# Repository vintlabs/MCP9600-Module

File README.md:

# MCP9600-Module
MCP9600 I²C Thermocouple to Digital Module (Hardware)

Simple module to detect temperature from a thermocouple on a Raspberry Pi (plugs in directly to the header on a Pi) or Arduino etc.
Supports thermocouple types K, J, T, N, S, E, B and R, and uses simple I²C interface. Can be run on 2.7v to 5.5v.
Board dimensions: 15x28mm (headers protrude beyond that)

There are headers on both sides of the board so that multiple boards can be connected together (being sure to use a different I2C address for each!), and there are footprints to add pullup resistors if they are required. 

Additionally, alerts can be programmed, and when plugged directly into a Raspberry Pi GPIO4 will be ALERT1, ALERT2-4 are accessible using optional header J3.

Note that as of this date, the gerbers are the Rev A prototype and the design is a bit ahead of that. (only minor edits - the Rev A board works fine)

Designed using KiCAD 5.0.0

See pdf/ directory for images and PDF of schematic.

See https://github.com/pvint/MCP9600_Pi for C code (tested on a Raspberry Pi Zero W using a type K thermocouple)

### Here are three boards in action. You can chain up to 8 boards on a single I²C bus.

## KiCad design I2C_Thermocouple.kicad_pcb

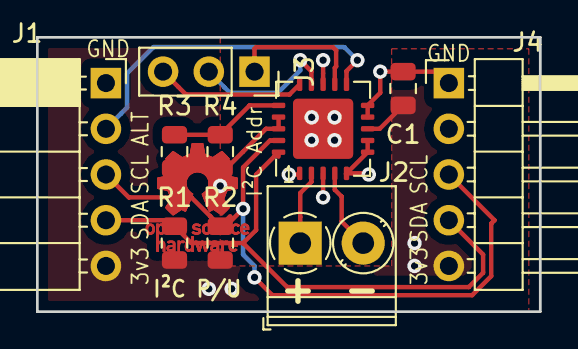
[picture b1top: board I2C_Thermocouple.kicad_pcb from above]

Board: 2 copper layers, 27.9 x 15.2 mm, 10 parts (0 on the bottom side), 11 nets.

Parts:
C1: 10uF; C_0805_2012Metric
J1: Conn_01x05; PinSocket_1x05_P2.54mm_Horizontal
J2: Screw_Terminal_01x02; TerminalBlock_Phoenix_PT-1,5-2-3.5-H_1x02_P3.50mm_Horizontal
J3: Conn_01x03; PinSocket_1x03_P2.54mm_Vertical
J4: Conn_01x05; PinHeader_1x05_P2.54mm_Horizontal
R1, R2, R3, R4: 10k; R_0805_2012Metric
U1: MCP9600; MCP9600_QFN-20-1EP_5x5mm_P0.65mm_EP3.35x3.35mm

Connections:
/ALERT2: J3.1, U1.12
ALERT1: J1.2, U1.11
Earth: C1.2, J1.1, J4.1, R4.2, U1.1, U1.3, U1.5, U1.6, U1.7, U1.9, U1.10, U1.13, U1.17, U1.18, U1.21
unnamed: J2.1, U1.2
unnamed: J2.2, U1.4
unnamed: J3.2, U1.14
unnamed: J3.3, U1.15
unnamed: R3.2, R4.1, U1.16
SCL: J1.3, J4.3, R2.2, U1.19
SDA: J1.4, J4.4, R1.2, U1.20
VDD: C1.1, J1.5, J4.5, R1.1, R2.1, R3.1, U1.8

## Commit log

2018-10-17 Initial import (Only a couple changes since Rev A sent to fab shop)
2018-10-17 dded images and schematic, README updates.
2018-10-19 Added +/- designations for thermocouple input
2018-10-20 readme update
2018-10-20 Added image of working boards
2018-10-23 Added CC-BY-SA license
